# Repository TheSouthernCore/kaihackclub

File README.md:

# Hackpad Macropad

This is a product I made in colaboration with Hackclub Blueprint and AMD

Its a simple Macropad that includes 2 RGB LEDs and 4 Keys

You will need a SEEED STUDIO RP2040 Microcontroller for this to work.

Both the STLs for the cacing and the PCB files are here. You need KiCad to view the PCB and need the SEEED STUDIO extensions aswell.  

Thank you for looking at my project :)

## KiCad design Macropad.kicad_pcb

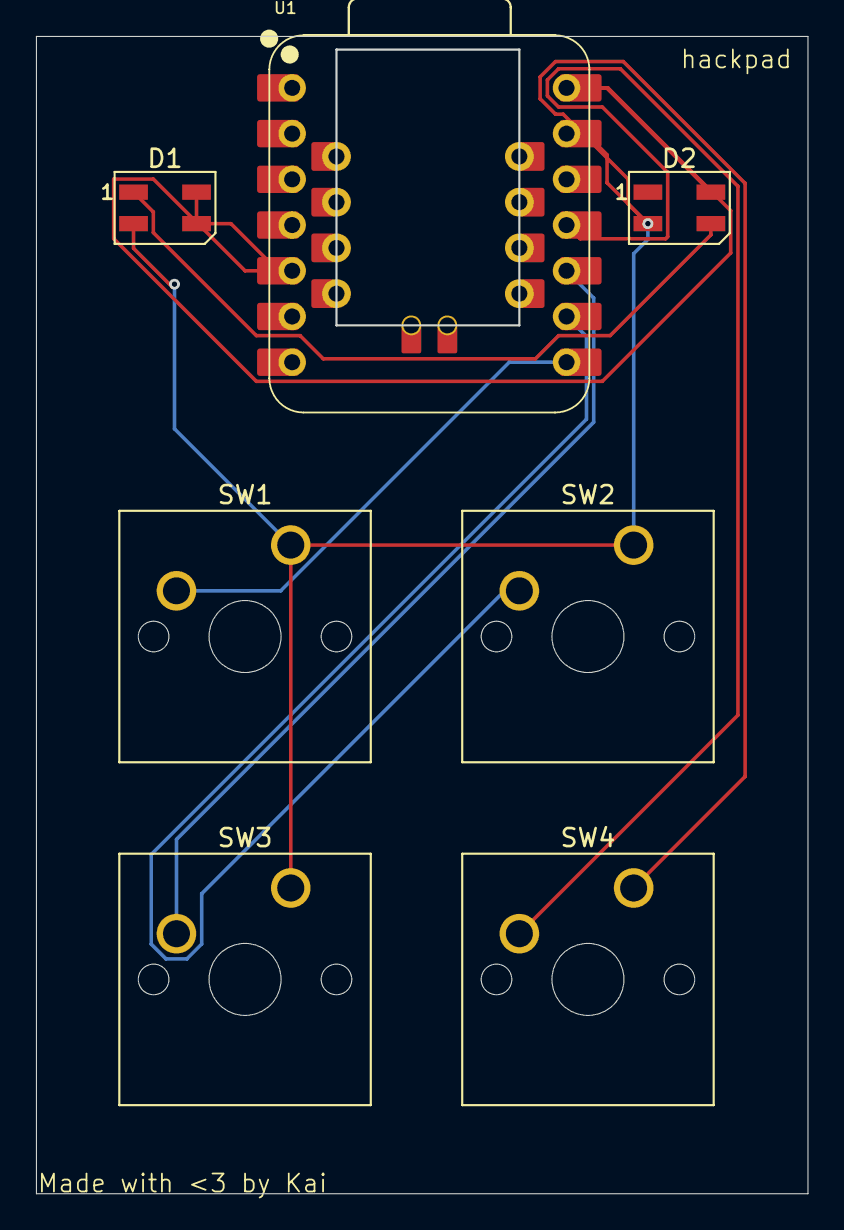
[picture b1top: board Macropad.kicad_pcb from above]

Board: 2 copper layers, 42.8 x 64.2 mm, 7 parts (0 on the bottom side), 7 nets.

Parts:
D1, D2: SK6812MINI; LED_SK6812MINI_PLCC4_3.5x3.5mm_P1.75mm
SW1, SW2, SW3, SW4: SW_Push; SW_Cherry_MX_1.00u_PCB
U1: XIAO-RP2040-DIP; XIAO-RP2350-DIP

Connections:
+5V: D1.3 (DIN), D1.4 (VDD), D2.4 (VDD), U1.5 (GPIO6/SDA), U1.14 (VBUS)
GND: D1.2 (VSS), D2.2 (VSS), SW1.1, SW2.1, SW3.1, SW4.1, U1.13 (GND)
unnamed: D1.1 (DOUT), D2.3 (DIN)
unnamed: SW1.2, U1.8 (GPIO1/RX)
unnamed: SW2.2, U1.9 (GPIO2/SCK)
unnamed: SW4.2, U1.11 (GPIO3/MOSI)
unnamed: SW3.2, U1.10 (GPIO4/MISO)

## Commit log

2025-12-04 Create Code for Macropad
2025-12-04 Rename Code for Macropad to Code for Macropad (RAW)
